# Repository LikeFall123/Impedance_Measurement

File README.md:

# Impedance Measurement
Project laboratory excercise - BME 2023/24/2 semester

The STM32F407 MCU calculates the impedance of the selected passive component, by measuring the excitation signal and the response.

Used techniques:\
  -ADC + DMA\
  -Real time Fourier transform (armmath.h)\
  -Model based sine parameter estimation

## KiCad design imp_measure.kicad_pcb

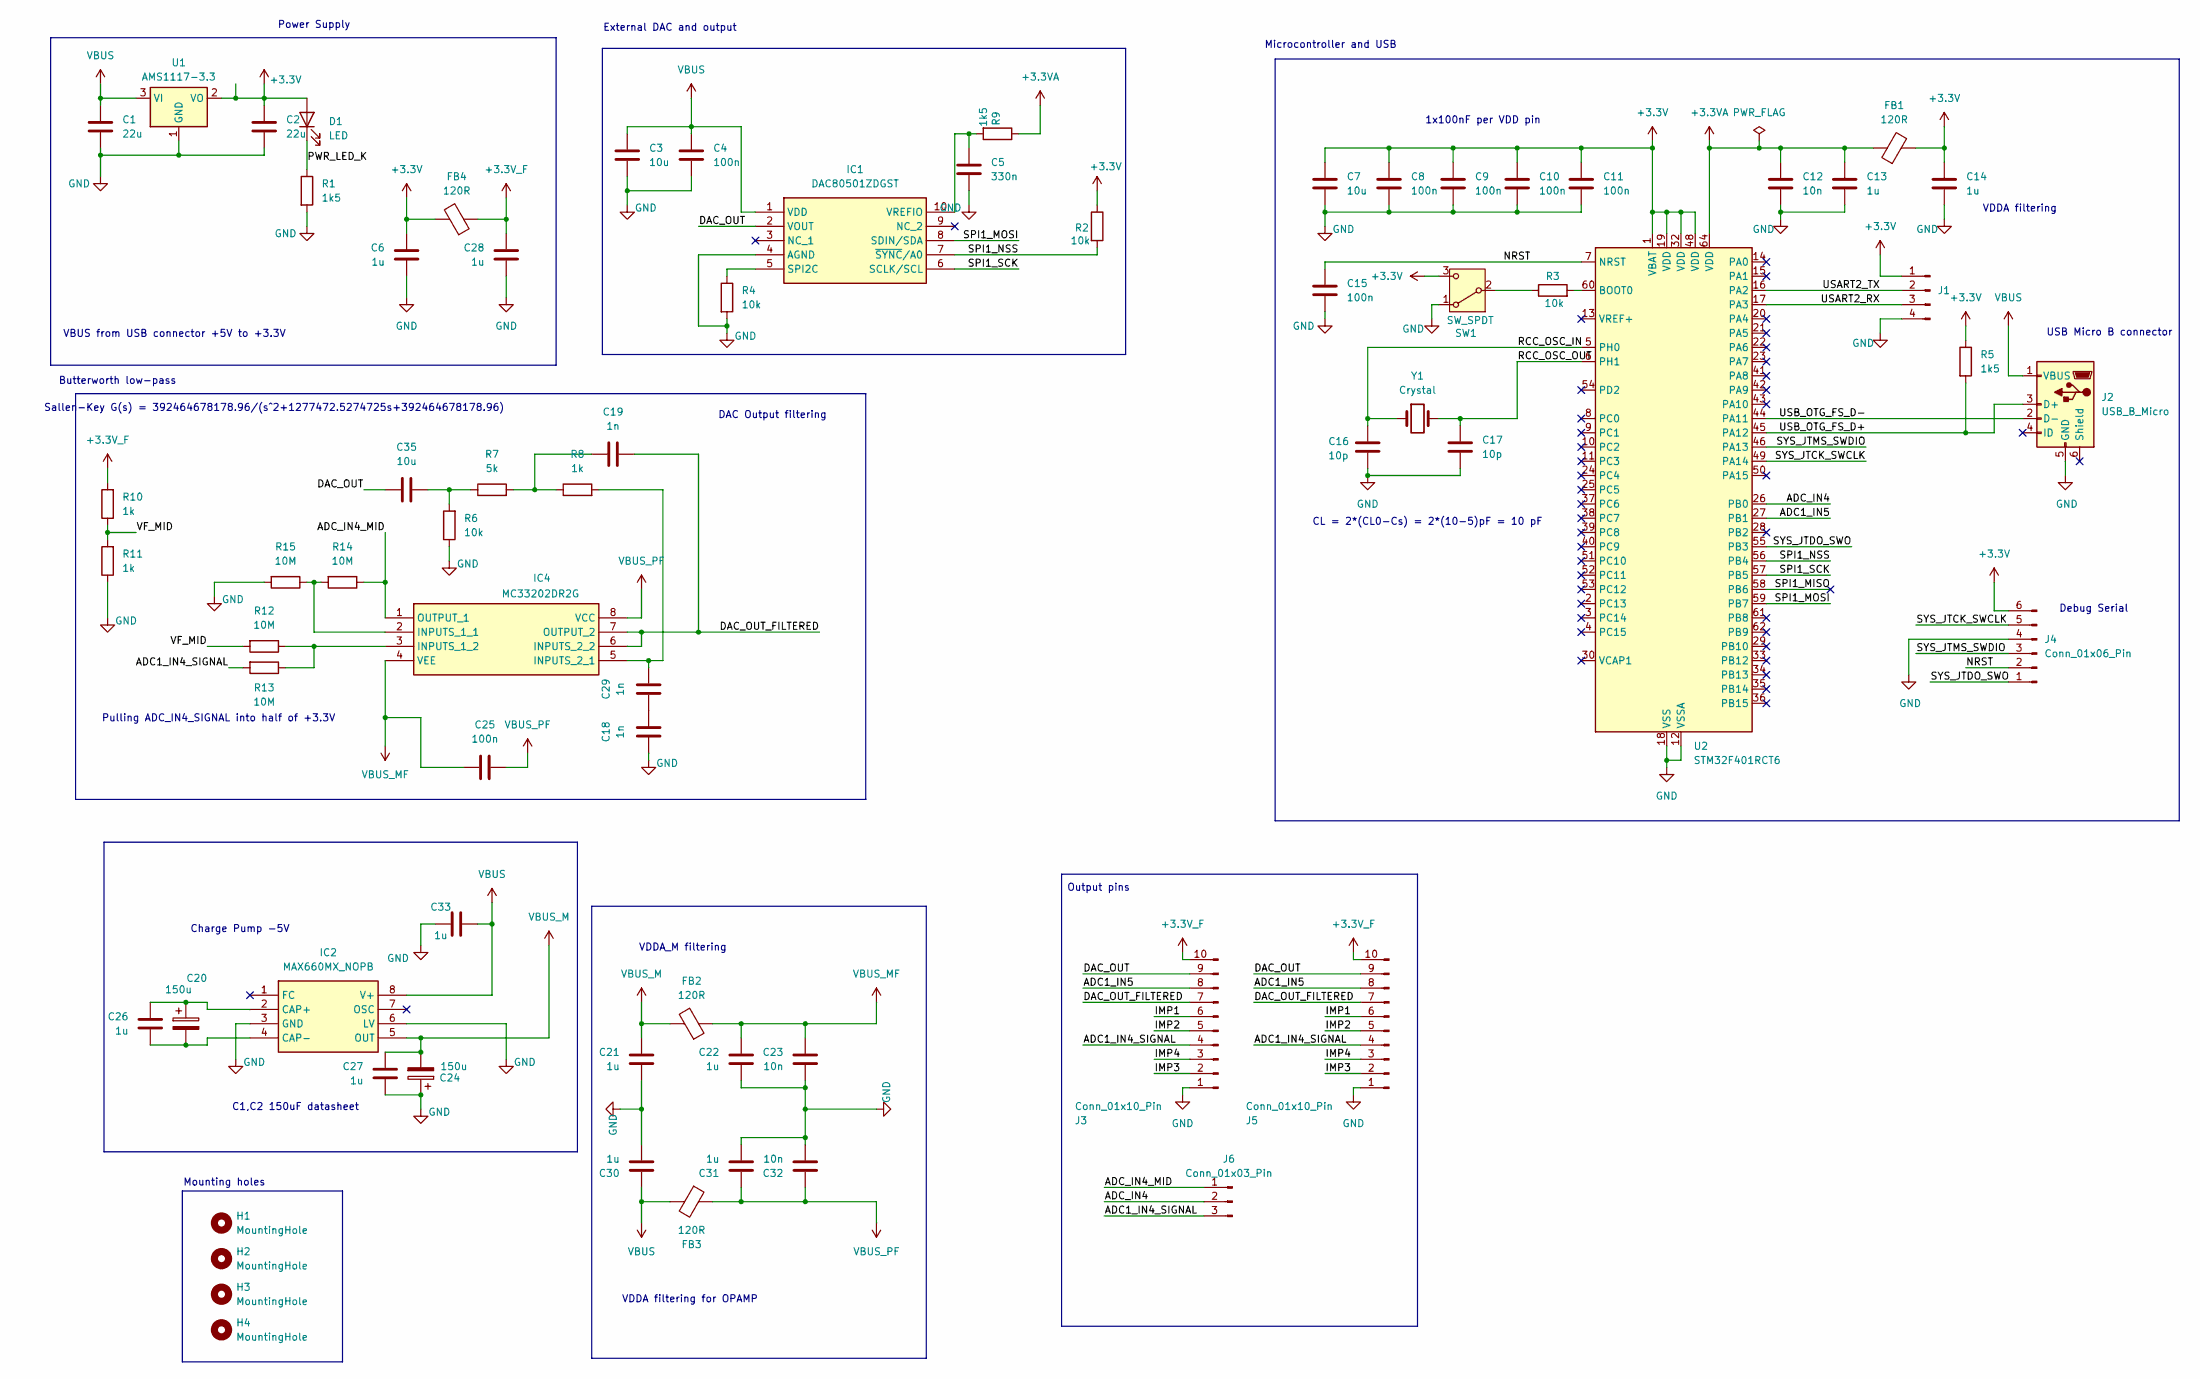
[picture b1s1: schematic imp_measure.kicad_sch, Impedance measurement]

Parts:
C1, C2: 22u; C_0805_2012Metric
C3, C7, C35: 10u; C_0805_2012Metric
C4, C8, C9, C10, C11, C15, C25: 100n; C_0805_2012Metric
C5: 330n; C_0805_2012Metric
C6, C13, C14, C21, C22, C26, C27, C28, C30, C31, C33: 1u; C_0805_2012Metric
C12, C23, C32: 10n; C_0805_2012Metric
C16, C17: 10p; C_0805_2012Metric
C18, C19, C29: 1n; C_0805_2012Metric
C20, C24: 150u; CP_Radial_D4.0mm_P1.50mm
D1: LED; LED_0805_2012Metric
FB1, FB2, FB3, FB4: 120R; L_0805_2012Metric
H1, H2, H3, H4: MountingHole; MountingHole_2mm
IC1: DAC80501ZDGST; SOP50P490X110-10N; Mouser Part Number 595-DAC80501ZDGST
IC2: MAX660MX_NOPB; SOIC127P600X175-8N; Mouser Part Number 926-MAX660MX/NOPB
IC4: MC33202DR2G; SOIC127P600X175-8N; Mouser Part Number 863-MC33202DR2G
J1: Conn_01x04_Pin; PinHeader_1x04_P2.54mm_Vertical
J2: USB_B_Micro; USB_Micro-B_Wuerth_629105150521
J3, J5: Conn_01x10_Pin; PinSocket_1x10_P2.54mm_Vertical
J4: Conn_01x06_Pin; PinHeader_1x06_P2.54mm_Vertical
J6: Conn_01x03_Pin; PinHeader_1x03_P2.54mm_Vertical
R1, R5, R9: 1k5; R_0805_2012Metric
R2, R3, R4, R6: 10k; R_0805_2012Metric
R7: 5k; R_0805_2012Metric
R8, R10, R11: 1k; R_0805_2012Metric
R12, R13, R14, R15: 10M; R_0805_2012Metric
SW1: SW_SPDT; SW_Slide-03_Wuerth-WS-SLTV_10x2.5x6.4_P2.54mm
U1: AMS1117-3.3; SOT-223-3_TabPin2
U2: STM32F401RCT6; LQFP-64_10x10mm_P0.5mm
Y1: Crystal; Crystal_HC49-U_Vertical

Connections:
+3.3V: C2.1, C6.1, C7.1, C8.1, C9.1, C10.1, C11.1, C14.1, D1.2 (A), FB1.2, FB4.2, J1.1, J4.6, R2.1, R5.1, SW1.3 (C), U1.2 (VO), U2.1 (VBAT), U2.19 (VDD), U2.32 (VDD), U2.48 (VDD)
+3.3VA: C12.1, C13.1, FB1.1, R9.1, U2.64 (VDD)
+3.3V_F: C28.1, FB4.1, J3.10, J5.10, R10.2
/ADC1_IN4_SIGNAL: J3.4, J5.4, J6.3, R13.2
/ADC1_IN5: J3.8, J5.8, U2.27 (PB1)
/ADC_IN4: J6.2, U2.26 (PB0)
/ADC_IN4_MID: IC4.1 (OUTPUT_1), J6.1, R14.1
/DAC_OUT: C35.1, IC1.2 (VOUT), J3.9, J5.9
/DAC_OUT_FILTERED: C19.2, IC4.6 (INPUTS_2_2), IC4.7 (OUTPUT_2), J3.7, J5.7
/IMP1: J3.6, J5.6
/IMP2: J3.5, J5.5
/IMP3: J3.2, J5.2
/IMP4: J3.3, J5.3
/NRST: C15.1, J4.2, U2.7 (NRST)
/PWR_LED_K: D1.1 (K), R1.1
/RCC_OSC_IN: C16.1, U2.5 (PH0), Y1.1
/RCC_OSC_OUT: C17.1, U2.6 (PH1), Y1.2
/SPI1_MISO: U2.58 (PB6)
/SPI1_MOSI: IC1.8 (SDIN/SDA), U2.59 (PB7)
/SPI1_NSS: IC1.7 (~SYNC/A0), R2.2, U2.56 (PB4)
/SPI1_SCK: IC1.6 (SCLK/SCL), U2.57 (PB5)
/SYS_JTCK_SWCLK: J4.5, U2.49 (PA14)
/SYS_JTDO_SWO: J4.1, U2.55 (PB3)
/SYS_JTMS_SWDIO: J4.3, U2.46 (PA13)
/USART2_RX: J1.3, U2.17 (PA3)
/USART2_TX: J1.2, U2.16 (PA2)
/USB_OTG_FS_D+: J2.3 (D+), R5.2, U2.45 (PA12)
/USB_OTG_FS_D-: J2.2 (D-), U2.44 (PA11)
/VF_MID: R10.1, R11.2, R12.2
GND: C1.2, C2.2, C3.2, C4.2, C5.2, C6.2, C7.2, C8.2, C9.2, C10.2, C11.2, C12.2, C13.2, C14.2, C15.2, C16.2, C17.2, C18.1, C21.2, C22.2, C23.2, C24.1, C27.2, C28.2, C30.2, C31.2, C32.2, C33.1, IC1.4 (AGND), IC2.3 (GND), IC2.6 (LV), J1.4, J2.5 (GND), J3.1, J4.4, J5.1, R1.2, R4.2, R6.1, R11.1, R15.2, SW1.1 (A), U1.1 (GND), U2.12 (VSSA), U2.18 (VSS), U2.31 (VSS), U2.47 (VSS), U2.63 (VSS)
unnamed: C18.2, C29.1
unnamed: C19.1, R7.2, R8.1
unnamed: C35.2, R6.2, R7.1
unnamed: IC1.5 (SPI2C), R4.1
unnamed: C5.1, IC1.10 (VREFIO), R9.2
unnamed: C20.1, C26.1, IC2.2 (CAP+)
unnamed: C20.2, C26.2, IC2.4 (CAP-)
unnamed: IC4.2 (INPUTS_1_1), R14.2, R15.1
unnamed: IC4.3 (INPUTS_1_2), R12.1, R13.1
unnamed: C29.2, IC4.5 (INPUTS_2_1), R8.2
unnamed: R3.1, SW1.2 (B)
unnamed: R3.2, U2.60 (BOOT0)
VBUS: C1.1, C3.1, C4.1, C30.1, C33.2, FB3.2, IC1.1 (VDD), IC2.8 (V+), J2.1 (VBUS), U1.3 (VI)
VBUS_M: C21.1, C24.2, C27.1, FB2.2, IC2.5 (OUT)
VBUS_MF: C22.1, C23.1, C25.2, FB2.1, IC4.4 (VEE)
VBUS_PF: C25.1, C31.1, C32.1, FB3.1, IC4.8 (VCC)

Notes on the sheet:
VDDA filtering for OPAMP
VBUS from USB connector +5V to +3.3V
VDDA_M filtering
C1,C2 150uF datasheet
1x100nF per VDD pin
Pulling ADC_IN4_SIGNAL into half of +3.3V
DAC Output filtering
External DAC and output
CL = 2*(CL0-Cs) = 2*(10-5)pF = 10 pF
Microcontroller and USB
Sallen-Key G(s) = 392464678178.96/(s^2+1277472.5274725s+392464678178.96)
Charge Pump -5V
Power Supply
Output pins
Mounting holes
USB Micro B connector
VDDA filtering
Butterworth low-pass
Debug Serial

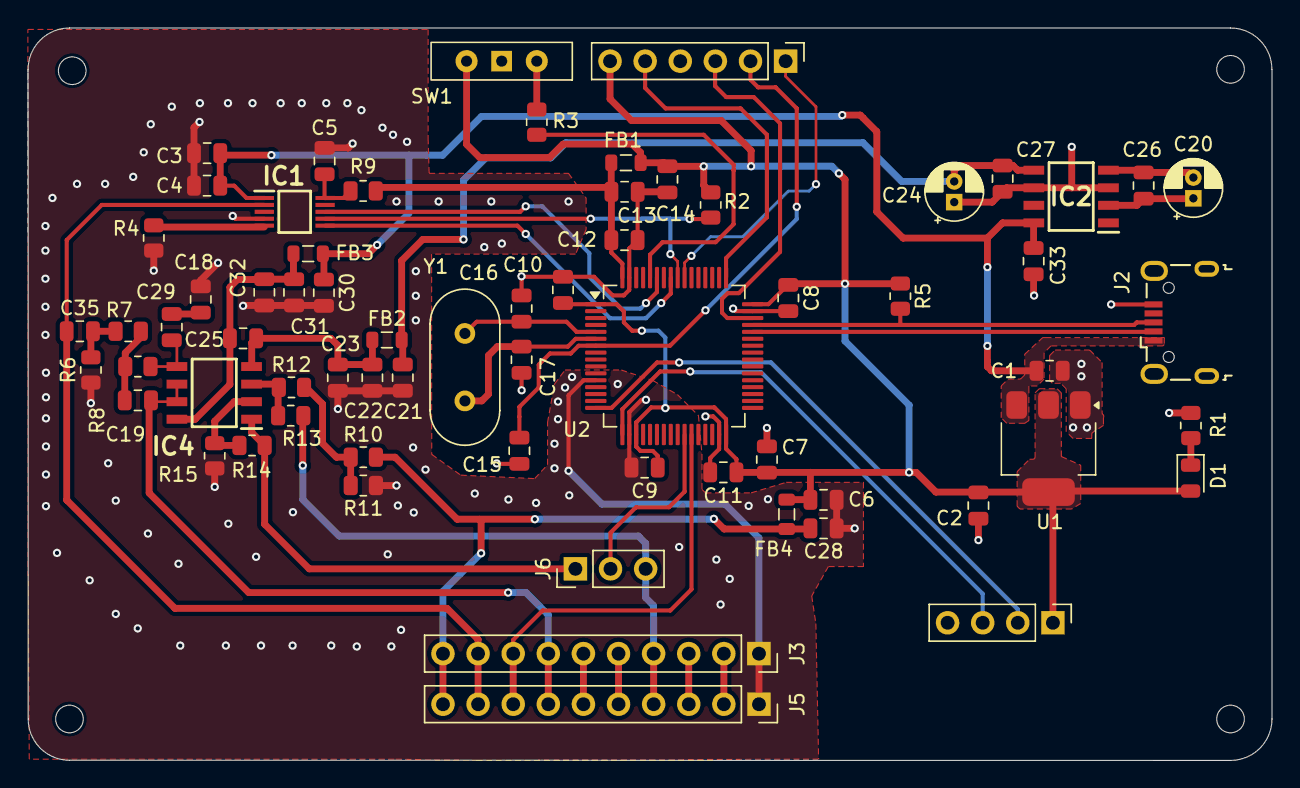
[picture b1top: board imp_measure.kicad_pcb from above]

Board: 2 copper layers, 90.0 x 53.0 mm, 71 parts (0 on the bottom side), 45 nets.

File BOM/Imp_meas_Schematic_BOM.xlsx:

Reference | Value | Datasheet | Footprint | Qty | DNP
C1,C2 | 22u | ~ | Capacitor_SMD:C_0805_2012Metric | 2
C3,C7 | 10u | ~ | Capacitor_SMD:C_0805_2012Metric | 2
C4,C8,C9,C10,C11,C15,C25 | 100n | ~ | Capacitor_SMD:C_0805_2012Metric | 7
C5 | 330n | ~ | Capacitor_SMD:C_0805_2012Metric | 1
C6,C13,C14,C21,C22,C26,C27,C28,C30,C31 | 1u | ~ | Capacitor_SMD:C_0805_2012Metric | 10
C12,C23,C32 | 10n | ~ | Capacitor_SMD:C_0805_2012Metric | 3
C16,C17 | 10p | ~ | Capacitor_SMD:C_0805_2012Metric | 2
C18,C19,C29 | 1n | ~ | Capacitor_SMD:C_0805_2012Metric | 3
C20,C24 | 150u | ~ | Capacitor_THT:CP_Radial_D4.0mm_P1.50mm | 2
D1 | LED | ~ | LED_SMD:LED_0805_2012Metric | 1
FB1,FB2,FB3,FB4 | 120R | ~ | Inductor_SMD:L_0805_2012Metric | 4
H1,H2,H3,H4 | MountingHole | ~ | MountingHole:MountingHole_2mm | 4
IC1 | DAC80501ZDGST | http://www.ti.com/lit/ds/symlink/dac60501.pdf | SamacSys_Parts:SOP50P490X110-10N | 1
IC2 | MAX660MX_NOPB | http://www.ti.com/lit/gpn/max660 | SamacSys_Parts:SOIC127P600X175-8N | 1
IC4 | MC33202DR2G | https://www.onsemi.com/pub/Collateral/MC33201-D.PDF | SamacSys_Parts:SOIC127P600X175-8N | 1
J1,J3,J5 | Conn_01x04_Pin | ~ | Connector_PinHeader_2.54mm:PinHeader_1x04_P2.54mm_Vertical | 3
J2 | USB_B_Micro | ~ | Connector_USB:USB_Micro-B_Wuerth_629105150521 | 1
J4 | Conn_01x06_Pin | ~ | Connector_PinHeader_2.54mm:PinHeader_1x06_P2.54mm_Vertical | 1
R1,R5 | 1k5 | ~ | Resistor_SMD:R_0805_2012Metric | 2
R2,R3,R4 | 10k | ~ | Resistor_SMD:R_0805_2012Metric | 3
R6,R7 | 3k3 | ~ | Resistor_SMD:R_0805_2012Metric | 2
R8 | 1k6 | ~ | Resistor_SMD:R_0805_2012Metric | 1
R9 | 1k | ~ | Resistor_SMD:R_0805_2012Metric | 1
SW1 | SW_SPDT | ~ | Button_Switch_THT:SW_Slide-03_Wuerth-WS-SLTV_10x2.5x6.4_P2.54mm | 1
U1 | AMS1117-3.3 | http://www.advanced-monolithic.com/pdf/ds1117.pdf | Package_TO_SOT_SMD:SOT-223-3_TabPin2 | 1
U2 | STM32F401RCT6 | https://www.st.com/resource/en/datasheet/stm32f401rc.pdf | Package_QFP:LQFP-64_10x10mm_P0.5mm | 1
Y1 | Crystal | ~ | Crystal:Crystal_HC49-U_Vertical | 1

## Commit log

2024-09-11 Add files via upload
    Initial schematic design in KiCad
2024-09-11 Add files via upload
    PDF of the schematic
2024-09-19 PCB design 1.0
2024-09-19 SCH pdf and PCB screenshot
2024-09-24 Ground fill for analog part
2024-09-24 Matlab and LTSpice simulation
    MATLAB simulation for the output filter. Quantized signal FFT.
    LTSpice model for DAC quantized outpu.
2024-09-24 Gerber changes
2024-10-04 PCB v1.2
    Changing the Multiple Feedback topology to Salen-Key.
2024-10-26 Forrasztáshoz
